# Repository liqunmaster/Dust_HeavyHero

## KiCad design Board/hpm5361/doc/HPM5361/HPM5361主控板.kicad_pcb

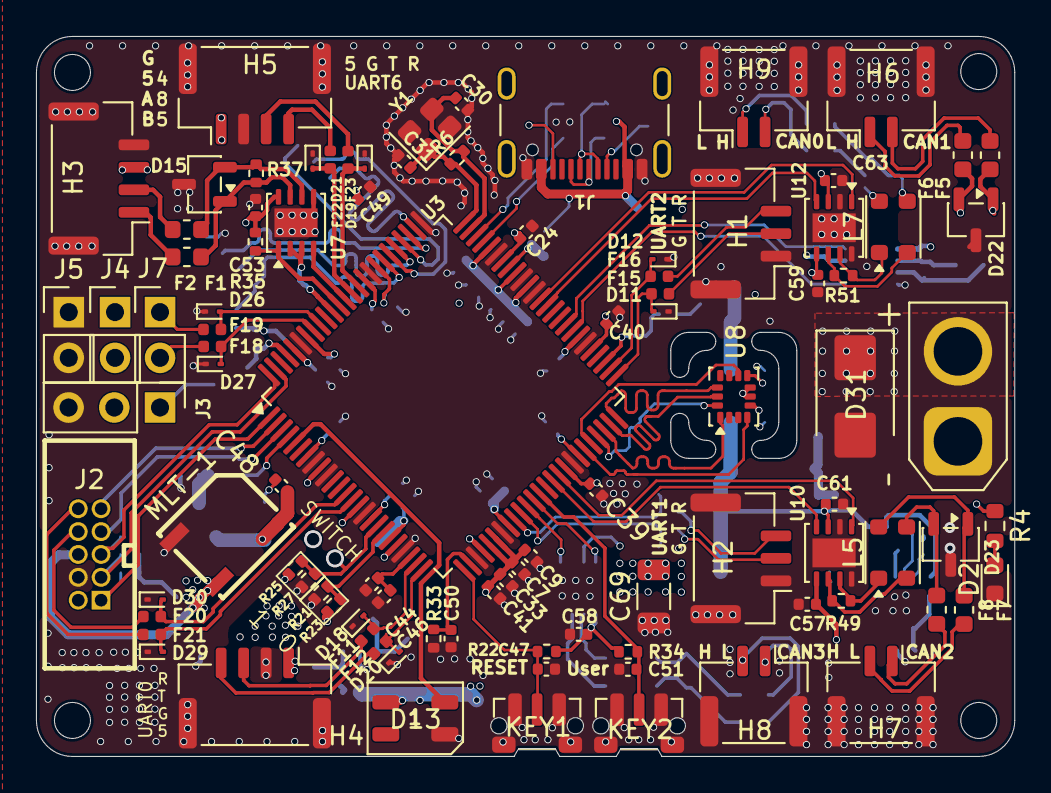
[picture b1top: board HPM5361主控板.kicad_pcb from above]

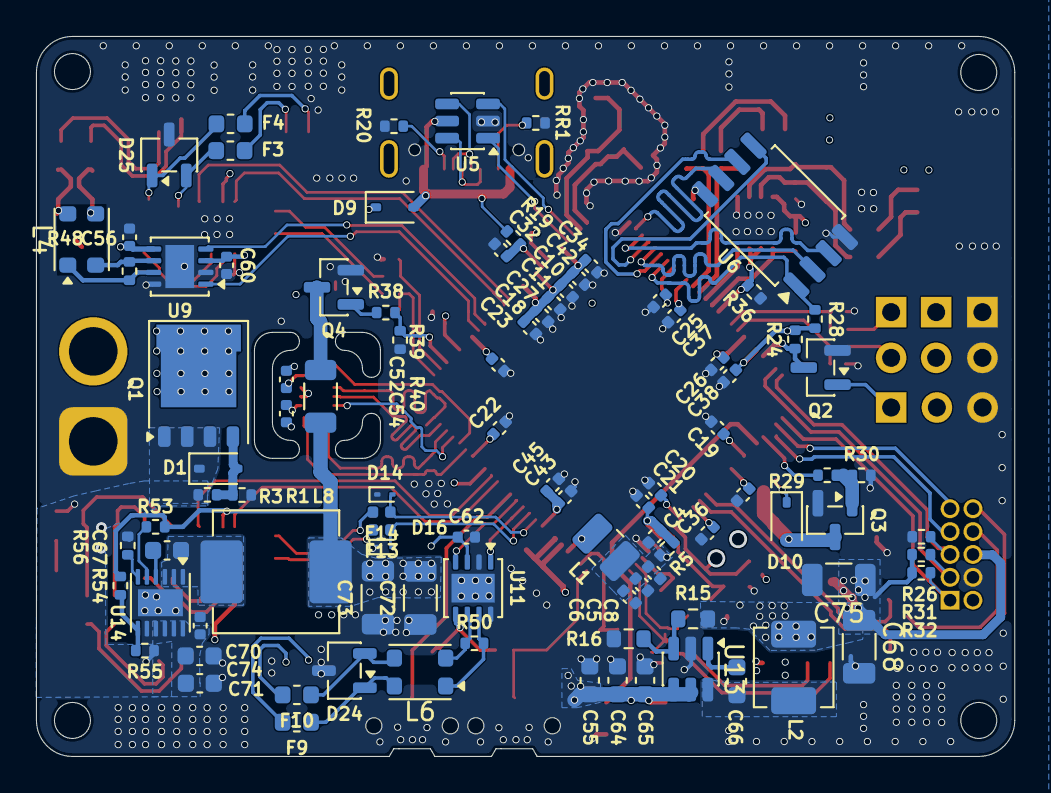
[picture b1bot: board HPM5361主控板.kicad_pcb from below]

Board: 4 copper layers, 54.3 x 40.0 mm, 189 parts (94 on the bottom side), 124 nets.

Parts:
C4, C34, C41: 10uF; C_0402_1005Metric
C5, C6, C9: 22uF; C_0402_1005Metric
C7, C8, C11, C18, C19, C20, C21, C22, C23, C24, C25, C26, C32, C33, C35, C36, C37, C38, C39, C40, C42, C43, C44, C47, C48, C49, C50, C51, C52, C53, C54, C56, C57, C58, C59, C60, C61, C62, C63, C70: 100nF; C_0402_1005Metric
C10, C27, C45, C46: 4.7uF; C_0402_1005Metric
C30, C31: 12pF; C_0402_1005Metric
C55, C64, C65: 10uF; C_0603_1608Metric
C66, C67: 100nF; C_0603_1608Metric
C68, C75: 22uF 10V; C_1206_3216Metric
C69: 47uF; C_1206_3216Metric
C71, C74: 4.7uF; C_0603_1608Metric
C72, C73: 22uF; C_1206_3216Metric
D1: BZT52C12S WH; D_SOD-323
D2: Blue; LED_0603_1608Metric
D9: SD103AWS; D_SOD-323
D10: SD103AWS S4; D_SOD-323
D11, D12, D14, D16, D18, D19, D20, D21, D26, D27, D29, D30: ESD9B5.0ST5G; D_SOD-923
D13: WS2812B; LED_WS2812B-Mini_PLCC4_3.5x3.5mm
D15: PSM712; SOT-23-3
D22, D23, D24, D25: PESD1CAN; SOT-23-3
D31: SMBJ30A; D_SMB
F1, F2, F3, F4, F5, F6, F7, F8, F9, F10: BSMD0603-005-15V; Fuse_0603_1608Metric
F11, F12, F13, F14, F15, F16, F18, F19, F20, F21, F22, F23: SMD0402; Fuse_0402_1005Metric
H1, H2: JST_GH_BM03B-GHS-TBT_1x03-1MP_P1.25mm_Vertical
H3, H4, H5: JST_GH_BM04B-GHS-TBT_1x04-1MP_P1.25mm_Vertical
H6, H7, H8, H9: JST_GH_BM02B-GHS-TBT_1x02-1MP_P1.25mm_Vertical
J1: USB_C_Receptacle_USB2.0_16P; USB_C_Receptacle_GCT_USB4105-xx-A_16P_TopMnt_Horizontal
J2: Conn_02x05_Counter_Clockwise_MountingPin; CONN-TH_10P-P1.27_HX-JN1.27-2X5P-ZZ-H4.9
J3: Conn_01x03_Pin; PinHeader_1x03_P2.54mm_Vertical
J4, J5, J7: Conn_01x02_Pin; PinHeader_1x02_P2.54mm_Vertical
KEY1, KEY2: 笑脸开关3*5; SW_Push_1P1T-MP_NO_Horizontal_Alps_SKRTLAE010
L1: NLV25T-4R7J-PF; L_1008_2520Metric
L2: 4.7uH; L_APV_APH0420
L4, L5, L6, L7: ACM2012(90欧); L_CommonModeChoke_Coilank_ACM3225
L8: 3.3UH; L_APV_APH0630
MLT-1: BUZ-SMD_L5.0-W5.5-P4.60
Q1: AGM60P100A; PQFN-8-EP_6x5mm_P1.27mm_Generic
Q2, Q3: PMBT3904; SOT-23
Q4: AO3404A; SOT-23
R1, R3, R19, R22, R26, R28, R30, R31, R32, R34, R35, R36, R39: 10K; R_0402_1005Metric
R4: 10K; R_0603_1608Metric
R5, R23, R25: 0; R_0402_1005Metric
R6: 1M; R_0402_1005Metric
R15: 62K; R_0603_1608Metric
R16: 20K; R_0603_1608Metric
R20, R24: 4.7K; R_0402_1005Metric
R21, R27, R33: 10k; R_0402_1005Metric
R29: 1K; R_0402_1005Metric
R37, R48, R49, R50, R51: 120; R_0402_1005Metric
R38: 33R; R_0402_1005Metric
R40: 36R; R_1206_3216Metric
R53, R54: 100K; R_0402_1005Metric
R55: 19.1K; R_0402_1005Metric
R56: 14.7K; R_0402_1005Metric
RR1: 4.7K; R_0402_1005Metric
U3: HPM5361ICB1; LQFP-100_14x14mm_P0.5mm
U5: USBLC6-2SC6; SOT-23-6
U6: W25Q128JVS; SOIC-8_5.3x5.3mm_P1.27mm
U7: SN65HVD75DRBR; VSON-8-1EP_3x3mm_P0.65mm_EP1.6x2.4mm
U8: ICM-42688P-HXY; LGA-14_3x2.5mm_P0.5mm_LayoutBorder3x4y
U9, U10, U11, U12: TJA1042TK-3; HVSON-8-1EP_3x3mm_P0.65mm_EP1.6x2.4mm
U13: RY8411; SOT-23-6
U14: LMR51450; WSON-12-1EP_3x3mm_P0.5mm_EP1.5x2.5mm
XT1: AMASS_XT30U-M_1x02_P5.0mm_Vertical
Y1: 24M; Crystal_SMD_2520-4Pin_2.5x2.0mm

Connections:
+3.3V: C7.2, C9.2, C10.1, C11.1, C18.2, C27.2, C33.1, C34.1, C35.2, C36.2, C37.2, C38.2, C39.2, C40.2, C41.1, C42.1, C48.1, C49.1, C52.1, C53.1, C54.1, C56.2, C57.2, C58.2, C59.2, C68.1, C75.1, D10.1 (K), J2.8, L2.2, MLT-1.1 (+), R15.2, R22.2, R23.2, R24.2, R25.2, R28.2, R31.2, R32.2, R34.2, R35.2, U3.9 (VIO_B00), U3.15 (VIO_B00), U3.30 (DCDC_IN), U3.31 (VPMC), U3.42 (VIO_B01), U3.55 (VIO_B01), U3.65 (VREFH), U3.67 (VANA), U3.71 (VPLL), U3.85 (VIO_B00), U3.96 (VIO_B00), U6.8 (VCC), U7.8 (VCC), U8.5 (VDDIO), U8.8 (VDD), U9.5 (VIO), U10.5 (VIO), U11.5 (VIO), U12.5 (VIO)
+5V: C55.1, C60.1, C61.1, C62.1, C63.1, C64.1, C65.1, C69.2, C72.2, C73.2, D9.1 (K), D13.1 (VDD), H3.3, H4.1, H5.1, J2.10, J3.2, J4.1, J4.2, L8.2, R40.1, R53.2, R54.2, U9.3 (VCC), U10.3 (VCC), U11.3 (VCC), U12.3 (VCC), U13.4 (EN), U13.5 (IN)
A: F2.2, H3.2
B: F1.2, H3.1
BOOT0: R21.1, R23.1, U3.19 (PA02/TMR1.COMP1/URT0.DE/URT0.RTS/I2C0.S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)
BOOT1: R25.1, R27.2, U3.18 (PA03/TMR1.CAPT1/URT0.CTS/I2C0.SDA/SPI3.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)
CAN0_H: F3.2, H9.2
CAN0_L: F4.2, H9.1
CAN0_RXD: U3.62 (PB01/TMR1.CAPT0/URT0.RXD/CAN0.RXD/PWM0.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), U12.4 (RXD)
CAN0_TXD: U3.63 (PB00/TMR1.COMP0/URT0.TXD/CAN0.TXD/PWM0.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), U12.1 (TXD)
CAN1_H: F5.2, H6.2
CAN1_L: F6.2, H6.1
CAN1_RXD: U3.59 (PB04/URT1.CTS/SPI3.CS0/CAN1.RXD/PWM0.P4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), U9.4 (RXD)
CAN1_TXD: U3.58 (PB05/TMR1.COMP2/URT1.DE/URT1.RTS/SPI3.S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), U9.1 (TXD)
CAN2_H: F7.2, H7.2
CAN2_L: F8.2, H7.1
CAN2_RXD: U3.40 (PY01/TMR3.CAPT0/URT0.RXD/CAN2.RXD/PWM0.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), U10.4 (RXD)
CAN2_TXD: U3.41 (PY00/TMR3.COMP0/URT0.TXD/CAN2.TXD/PWM0.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), U10.1 (TXD)
CAN3_H: F9.2, H8.2
CAN3_L: F10.2, H8.1
CAN3_RXD: U3.37 (PY04/URT1.CTS/SPI2.CS0/CAN3.RXD/PWM0.P4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), U11.4 (RXD)
CAN3_TXD: U3.36 (PY05/TMR3.COMP2/URT1.DE/URT1.RTS/SPI2.S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), U11.1 (TXD)
DBUS: J3.1, Q2.1 (B)
DCDC_LP: L1.2, U3.29 (DCDC_LP)
GND: C4.1, C5.1, C6.1, C7.1, C8.1, C9.1, C10.2, C11.2, C18.1, C19.2, C20.2, C21.2, C22.2, C23.2, C24.2, C25.2, C26.2, C27.1, C30.2, C31.1, C32.1, C33.2, C34.2, C35.1, C36.1, C37.1, C38.1, C39.1, C40.1, C41.2, C42.2, C43.1, C44.1, C45.1, C46.1, C47.2, C49.2, C50.1, C51.2, C52.2, C53.2, C54.2, C55.2, C56.1, C57.1, C58.1, C59.1, C60.2, C61.2, C62.2, C63.2, C64.2, C65.2, C68.2, C69.1, C70.1, C71.1, C72.1, C73.1, C74.1, C75.2, D2.1 (K), D11.1 (A1), D12.1 (A1), D13.3 (VSS), D14.1 (A1), D15.3 (A), D16.1 (A1), D18.1 (A1), D19.1 (A1), D20.1 (A1), D21.1 (A1), D22.3 (A), D23.3 (A), D24.3 (A), D25.3 (A), D26.1 (A1), D27.1 (A1), D29.1 (A1), D30.1 (A1), D31.2 (A2), H1.1, H1.MP, H2.1, H2.MP, H3.4, H3.MP, H4.2, H4.MP, H5.2, H5.MP, H6.MP, H7.MP, H8.MP, H9.MP, J1.A1 (GND), J1.A12 (GND), J1.B1 (GND), J1.B12 (GND), J2.9, J3.3, J5.1, J5.2, KEY1.1, KEY1.MP, KEY2.1, KEY2.MP, MLT-1.3 (NC), Q2.2 (E), Q3.2 (E), Q4.2 (S), R1.2, R16.1, R20.2, R21.2, R26.2, R27.1, R30.2, R33.1, R36.1, R39.1, R55.1, R56.1, RR1.2, U3.8 (VSS), U3.10 (VSS), U3.16 (VSS), U3.22 (VSS), U3.28 (DCDC_GND), U3.32 (VSS), U3.43 (VSS), U3.56 (VSS), U3.64 (VREFL), U3.66 (VSS), U3.70 (VSS), U3.76 (VSS), U3.84 (VSS), U3.95 (VSS), U5.2 (GND), U6.4 (GND), U7.5 (GND), U7.9 (PAD), U8.6 (GNDIO), U8.7 (GND), U9.2 (GND), U9.8 (STB), U9.9 (GND), U10.2 (GND), U10.8 (STB), U10.9 (GND), U11.2 (GND), U11.8 (STB), U11.9 (GND), U12.2 (GND), U12.8 (STB), U12.9 (GND), U13.2 (GND), U14.8 (GND), U14.13 (PAD), XT1.1 (-), Y1.2, Y1.4
INT1: U3.45 (PB15/TMR0.COMP3/URT3.TXD/SPI2.DAT3/CAN3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), U8.4 (INT1)
INT2: U3.46 (PB14/URT3.RXD/SPI2.DAT2/CAN3.RXD/PWM0.F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), U8.9 (INT2)
JTAG_TCK: J2.3, R26.1, U3.100 (PA06/TMR0.CAPT0/URT1.RXD/I2C1.SDA/SPI0.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)
JTAG_TDI: J2.1, R32.1, U3.1 (PA05/TMR1.COMP2/URT1.DE/URT1.RTS/SPI0.S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)
JTAG_TDO: J2.5, U3.2 (PA04/URT1.CTS/SPI0.CS0/CAN1.RXD/PWM0.P0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)
JTAG_TMS: J2.2, R31.1, U3.99 (PA07/TMR0.COMP0/URT1.TXD/I2C1.SCL/SPI0.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)
JTAG_TRST: J2.4, U3.3 (PA08/TMR0.COMP1/URT2.TXD/I2C2.SCL/SPI3.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)
unnamed: C67.2, L8.1, U14.1 (SW), U14.2 (SW), U14.3 (SW)
unnamed: D1.2 (A), Q1.G, R1.1, R3.2
unnamed: D2.2 (A), R4.2
unnamed: C48.2, D10.2 (A), MLT-1.2 (-), Q3.3 (C)
unnamed: D22.1 (K), F5.1, L4.4
unnamed: D22.2 (K), F6.1, L4.3
unnamed: D23.1 (K), F7.1, L5.4
unnamed: D23.2 (K), F8.1, L5.3
unnamed: D24.1 (K), F9.1, L6.4
unnamed: D24.2 (K), F10.1, L6.3
unnamed: D25.1 (K), F4.1, L7.3
unnamed: D25.2 (K), F3.1, L7.4
unnamed: F11.2, H4.3
unnamed: F12.2, H4.4
unnamed: F13.2, H2.2
unnamed: F14.2, H2.3
unnamed: F15.2, H1.2
unnamed: F16.2, H1.3
unnamed: F22.2, H5.3
unnamed: F23.2, H5.4
unnamed: J1.A5 (CC1), R20.1
unnamed: J1.B5 (CC2), RR1.1
unnamed: J1.A6 (D+), J1.B6 (D+), U5.6 (I/O1)
unnamed: J1.A7 (D-), J1.B7 (D-), U5.4 (I/O2)
unnamed: F21.1, J2.6
unnamed: F20.1, J2.7
unnamed: F19.2, J7.1
unnamed: F18.2, J7.2
unnamed: Q3.1 (B), R29.1, R30.1
unnamed: Q4.3 (D), R40.2
unnamed: Q4.1 (G), R38.1
unnamed: C5.2, C6.2, C8.2, L1.1, R5.2, U3.21 (DCDC_SNS)
unnamed: C32.2, R19.2, U3.68 (USBVBUS)
unnamed: C30.1, R6.2, U3.74 (XTALI), Y1.3
unnamed: C31.2, R6.1, U3.75 (XTALO), Y1.1
unnamed: C44.2, C46.2, U3.23 (VDD_OTPCAP)
unnamed: C43.2, C45.2, U3.33 (VDD_PMCCAP)
unnamed: D15.2 (K), F2.1, R37.1, U7.6 (A)
unnamed: D15.1 (K), F1.1, R37.2, U7.7 (B)
unnamed: L4.1, R48.2, U9.7 (CANH)
unnamed: L4.2, R48.1, U9.6 (CANL)
unnamed: L5.1, R49.2, U10.7 (CANH)
unnamed: L5.2, R49.1, U10.6 (CANL)
unnamed: L6.1, R50.2, U11.7 (CANH)
unnamed: L6.2, R50.1, U11.6 (CANL)
unnamed: L7.1, R51.2, U12.7 (CANH)
unnamed: L7.2, R51.1, U12.6 (CANL)
unnamed: C66.2, U13.1 (BS)
unnamed: R15.1, R16.2, U13.3 (FB)
unnamed: C66.1, L2.1, U13.6 (LX)
unnamed: C67.1, U14.4 (BOOT)
unnamed: R54.1, R55.2, U14.7 (FB)
unnamed: R53.1, U14.5 (PG)
unnamed: R56.2, U14.6 (RT)
PWM0_P5: R29.2, U3.4 (PA09/TMR0.CAPT1/URT2.RXD/I2C2.SDA/SPI3.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)
PWM0_P6: D13.4 (DIN), U3.5 (PA10/TMR0.COMP2/URT2.DE/URT2.RTS/SPI3.C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)
PWM0_P7: R38.2, R39.2, U3.53 (PB07/TMR0.COMP0/URT1.TXD/I2C1.SCL/SPI3.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)
PWM1_P2: D27.2 (A2), F18.1, U3.93 (PA18/TMR3.COMP1/URT4.DE/URT4.RTS/I2C0.S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)
PWM1_P3: D26.2 (A2), F19.1, U3.92 (PA19/TMR3.CAPT1/URT4.CTS/I2C0.SDA/SPI1.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)
RESET: C47.1, KEY1.2, R22.1, U3.26 (RESETN)
SPI1_CS: R28.1, U3.82 (PA26/TMR2.COMP2/URT6.DE/URT6.RTS/SPI1.C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), U6.1 (~CS)
SPI1_D2: U3.78 (PA30/URT7.RXD/SPI1.DAT2/CAN3.RXD/XPI0.C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), U6.3 (~WP/IO_{2})
SPI1_D3: U3.77 (PA31/TMR2.COMP3/URT7.TXD/SPI1.DAT3/CAN3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), U6.7 (~HOLD/~RESET/IO_{3})
SPI1_MISO: U3.80 (PA28/URT7.CTS/I2C3.SDA/SPI1.MISO/XPI0.C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), U6.2 (DO/IO_{1})
SPI1_MOSI: U3.79 (PA29/TMR3.COMP3/URT7.DE/URT7.RTS/I2C3.S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), U6.5 (DI/IO_{0})
SPI1_SCLK: U3.81 (PA27/URT6.CTS/SPI1.SCLK/XPI0.CA_SCLK/PW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), U6.6 (CLK)
SPI2_CS: U3.50 (PB10/TMR0.COMP2/URT2.DE/URT2.RTS/SPI2.C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), U8.12 (CSB)
SPI2_MISO: U3.48 (PB12/URT3.CTS/I2C3.SDA/SPI2.MISO/PWM1.F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), U8.1 (SDO/SA0)
SPI2_MOSI: U3.47 (PB13/TMR1.COMP3/URT3.DE/URT3.RTS/I2C3.S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), U8.14 (SDX)
SPI2_SCLK: U3.49 (PB11/URT2.CTS/SPI2.SCLK/ACMP.COMP1/PWM1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), U8.13 (SCX)
UART0_RXD: D18.2 (A2), F11.1, U3.24 (PA01/TMR1.CAPT0/URT0.RXD/CAN0.RXD/PWM0.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)
UART0_TXD: D20.2 (A2), F12.1, U3.25 (PA00/TMR1.COMP0/URT0.TXD/CAN0.TXD/PWM0.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)
UART1_RXD: D16.2 (A2), F13.1, U3.35 (PY06/TMR2.CAPT0/URT1.RXD/I2C3.SDA/SPI2.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)
UART1_TXD: D14.2 (A2), F14.1, U3.34 (PY07/TMR2.COMP0/URT1.TXD/I2C3.SCL/SPI2.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)
UART2_RXD: D11.2 (A2), F15.1, U3.51 (PB09/TMR0.CAPT1/URT2.RXD/I2C2.SDA/SPI2.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)
UART2_TXD: D12.2 (A2), F16.1, U3.52 (PB08/TMR0.COMP1/URT2.TXD/I2C2.SCL/SPI2.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)
UART3_RXD: D30.2 (A2), F20.2, U3.13 (PA14/URT3.RXD/SPI3.DAT2/CAN3.RXD/PWM0.P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)
UART3_TXD: D29.2 (A2), F21.2, U3.14 (PA15/TMR0.COMP3/URT3.TXD/SPI3.DAT3/CAN3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)
UART4_RXD: Q2.3 (C), R24.1, U3.97 (PA17/TMR3.CAPT0/URT4.RXD/CAN0.RXD/PWM0.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)
UART5_DE: R36.2, U3.90 (PA21/TMR3.COMP2/URT5.DE/URT5.RTS/SPI2.S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), U7.2 (#RE), U7.3 (DE)
UART5_RXD: R35.1, U3.89 (PA22/TMR2.CAPT0/URT5.RXD/I2C1.SDA/SPI2.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), U7.1 (R_OUT)
UART5_TXD: U3.88 (PA23/TMR2.COMP0/URT5.TXD/I2C1.SCL/SPI2.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), U7.4 (D_IN)
UART6_RXD: D19.2 (A2), F22.1, U3.86 (PA25/TMR2.CAPT1/URT6.RXD/I2C2.SDA/SPI1.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)
UART6_TXD: D21.2 (A2), F23.1, U3.87 (PA24/TMR2.COMP1/URT6.TXD/I2C2.SCL/SPI1.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)
USB_DM: U3.73 (USB_DM), U5.3 (I/O2)
USB_DP: U3.72 (USB_DP), U5.1 (I/O1)
User_Key: C51.1, KEY2.2, R34.1, U3.38 (PY03/TMR3.CAPT1/URT0.CTS/I2C2.SDA/CAN3.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)
VBUS: D9.2 (A), J1.A4 (VBUS), J1.A9 (VBUS), J1.B4 (VBUS), J1.B9 (VBUS), R19.1, U5.5 (VBUS)
VDD_SOC: C4.2, C19.1, C20.1, C21.1, C22.1, C23.1, C24.1, C25.1, C26.1, R5.1, U3.7 (VDD_SOC), U3.17 (VDD_SOC), U3.20 (VDD_SOC), U3.44 (VDD_SOC), U3.57 (VDD_SOC), U3.69 (VDD_SOC), U3.83 (VDD_SOC), U3.94 (VDD_SOC)
VIN: C70.2, C71.2, C74.2, D1.1 (K), Q1.S, R3.1, R4.1, U14.9 (EN), U14.10 (VIN), U14.11 (VIN), U14.12 (VIN)
VIN1: D31.1 (A1), Q1.D, XT1.2 (+)
WAKEUP: C50.2, R33.2, U3.27 (WAKEUP)

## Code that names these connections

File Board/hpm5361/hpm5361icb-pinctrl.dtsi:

/*
 * Copyright 2026 Dust Robotics
 * SPDX-License-Identifier: Apache-2.0
 *
 * Dust HeavyHero HPM5361ICB pinmux definitions.
 * Default wiring from the board schematic. Application overlays may replace
 * a peripheral state when a different operating mode is required.
 */

#include "dt-bindings/pinctrl/hpmicro-pinctrl-common.h"

&pinctrl {
	/* UART0 ISP header: PA00 TX, PA01 RX. */
	pinmux_uart0: pinmux_uart0 {
		group0 {
			pinmux = <HPMICRO_PINMUX(HPMICRO_PIN(HPMICRO_PORTA, 0), IOC_TYPE_IOC, 0, 2)>,
				 <HPMICRO_PINMUX(HPMICRO_PIN(HPMICRO_PORTA, 1), IOC_TYPE_IOC, 0, 2)>;
		};
	};

	/* UART1 external header: PY07 TX, PY06 RX. */
	pinmux_uart1: pinmux_uart1 {
		group0 {
			pinmux = <HPMICRO_PINMUX(HPMICRO_PIN(HPMICRO_PORTY, 7), IOC_TYPE_IOC, 0, 2)>,
				 <HPMICRO_PINMUX(HPMICRO_PIN(HPMICRO_PORTY, 6), IOC_TYPE_IOC, 0, 2)>;
		};
	};

	/* UART2: VT02/VT03 shared figure-transmission interface (PB08/PB09 ALT2) */
	pinmux_uart2: pinmux_uart2 {
		group0 {
			pinmux = <HPMICRO_PINMUX(HPMICRO_PIN(HPMICRO_PORTB, 8), IOC_TYPE_IOC, 0, 2)>,
				 <HPMICRO_PINMUX(HPMICRO_PIN(HPMICRO_PORTB, 9), IOC_TYPE_IOC, 0, 2)>;
		};
	};

	/* UART3: debug console / redefined printf (PA14/PA15 ALT2) */
	pinmux_uart3: pinmux_uart3 {
		group0 {
			pinmux = <HPMICRO_PINMUX(HPMICRO_PIN(HPMICRO_PORTA, 14), IOC_TYPE_IOC, 0, 2)>,
				 <HPMICRO_PINMUX(HPMICRO_PIN(HPMICRO_PORTA, 15), IOC_TYPE_IOC, 0, 2)>;
		};
	};

	/* UART4: DT7 remote receiver (PA16/PA17 ALT2) */
	pinmux_uart4: pinmux_uart4 {
		group0 {
			pinmux = <HPMICRO_PINMUX(HPMICRO_PIN(HPMICRO_PORTA, 16), IOC_TYPE_IOC, 0, 2)>,
				 <HPMICRO_PINMUX(HPMICRO_PIN(HPMICRO_PORTA, 17), IOC_TYPE_IOC, 0, 2)>;
		};
	};

	/* UART5: PA23 TX, PA22 RX, PA21 DE. */
	pinmux_uart5: pinmux_uart5 {
		group0 {
			pinmux = <HPMICRO_PINMUX(HPMICRO_PIN(HPMICRO_PORTA, 23), IOC_TYPE_IOC, 0, 2)>,
				 <HPMICRO_PINMUX(HPMICRO_PIN(HPMICRO_PORTA, 22), IOC_TYPE_IOC, 0, 2)>,
				 <HPMICRO_PINMUX(HPMICRO_PIN(HPMICRO_PORTA, 21), IOC_TYPE_IOC, 0, 2)>;
		};
	};

	/* UART6: PA24 TX, PA25 RX. */
	pinmux_uart6: pinmux_uart6 {
		group0 {
			pinmux = <HPMICRO_PINMUX(HPMICRO_PIN(HPMICRO_PORTA, 24), IOC_TYPE_IOC, 0, 2)>,
				 <HPMICRO_PINMUX(HPMICRO_PIN(HPMICRO_PORTA, 25), IOC_TYPE_IOC, 0, 2)>;
		};
	};

	/* SPI1: W25Q128 log flash, including the quad data pins. */
	pinmux_spi1: pinmux_spi1 {
		group0 {
			pinmux = <HPMICRO_PINMUX(HPMICRO_PIN(HPMICRO_PORTA, 26), IOC_TYPE_IOC, 0, 5)>,
				 <HPMICRO_PINMUX(HPMICRO_PIN(HPMICRO_PORTA, 27), IOC_TYPE_IOC, 0, 5)>,
				 <HPMICRO_PINMUX(HPMICRO_PIN(HPMICRO_PORTA, 28), IOC_TYPE_IOC, 0, 5)>,
				 <HPMICRO_PINMUX(HPMICRO_PIN(HPMICRO_PORTA, 29), IOC_TYPE_IOC, 0, 5)>,
				 <HPMICRO_PINMUX(HPMICRO_PIN(HPMICRO_PORTA, 30), IOC_TYPE_IOC, 0, 5)>,
				 <HPMICRO_PINMUX(HPMICRO_PIN(HPMICRO_PORTA, 31), IOC_TYPE_IOC, 0, 5)>;
		};
	};

	/* SPI2: ICM-42688P-HXY IMU (PB13/12/11/10 = MOSI/MISO/SCLK/CS_0 ALT5) */
	pinmux_spi2: pinmux_spi2 {
		group0 {
			pinmux = <HPMICRO_PINMUX(HPMICRO_PIN(HPMICRO_PORTB, 13), IOC_TYPE_IOC, 0, 5)>,
				 <HPMICRO_PINMUX(HPMICRO_PIN(HPMICRO_PORTB, 12), IOC_TYPE_IOC, 0, 5)>,
				 <HPMICRO_PINMUX(HPMICRO_PIN(HPMICRO_PORTB, 11), IOC_TYPE_IOC, 0, 5)>,
				 <HPMICRO_PINMUX(HPMICRO_PIN(HPMICRO_PORTB, 10), IOC_TYPE_IOC, 0, 5)>;
		};
	};

	pinmux_board_can0: pinmux_board_can0 {
		group0 {
			pinmux = <HPMICRO_PINMUX(HPMICRO_PIN(HPMICRO_PORTB, 0), IOC_TYPE_IOC, 0, 7)>,
				 <HPMICRO_PINMUX(HPMICRO_PIN(HPMICRO_PORTB, 1), IOC_TYPE_IOC, 0, 7)>;
		};
	};

	pinmux_board_can1: pinmux_board_can1 {
		group0 {
			pinmux = <HPMICRO_PINMUX(HPMICRO_PIN(HPMICRO_PORTB, 5), IOC_TYPE_IOC, 0, 7)>,
				 <HPMICRO_PINMUX(HPMICRO_PIN(HPMICRO_PORTB, 4), IOC_TYPE_IOC, 0, 7)>;
		};
	};

	pinmux_board_can2: pinmux_board_can2 {
		tx {
			pinmux = <HPMICRO_PINMUX(HPMICRO_PIN(HPMICRO_PORTY, 0), IOC_TYPE_IOC, 0, 7)>;
		};
		rx {
			pinmux = <HPMICRO_PINMUX(HPMICRO_PIN(HPMICRO_PORTY, 1), IOC_TYPE_IOC, 0, 7)>;
			input-enable;
		};
		pioc {
			pinmux = <HPMICRO_PINMUX(HPMICRO_PIN(HPMICRO_PORTY, 0), IOC_TYPE_PIOC, 0, 3)>,
				 <HPMICRO_PINMUX(HPMICRO_PIN(HPMICRO_PORTY, 1), IOC_TYPE_PIOC, 0, 3)>;
		};
	};

	pinmux_board_can3: pinmux_board_can3 {
		tx {
			pinmux = <HPMICRO_PINMUX(HPMICRO_PIN(HPMICRO_PORTY, 5), IOC_TYPE_IOC, 0, 7)>;
		};
		rx {
			pinmux = <HPMICRO_PINMUX(HPMICRO_PIN(HPMICRO_PORTY, 4), IOC_TYPE_IOC, 0, 7)>;
			input-enable;
		};
		pioc {
			pinmux = <HPMICRO_PINMUX(HPMICRO_PIN(HPMICRO_PORTY, 5), IOC_TYPE_PIOC, 0, 3)>,
				 <HPMICRO_PINMUX(HPMICRO_PIN(HPMICRO_PORTY, 4), IOC_TYPE_PIOC, 0, 3)>;
		};
	};

	/* PWM0: PA09 P5, PA10 P6, PB07 P7. */
	pinmux_pwm0: pinmux_pwm0 {
		group0 {
			pinmux = <HPMICRO_PINMUX(HPMICRO_PIN(HPMICRO_PORTA, 9), IOC_TYPE_IOC, 0, 16)>,
				 <HPMICRO_PINMUX(HPMICRO_PIN(HPMICRO_PORTA, 10), IOC_TYPE_IOC, 0, 16)>,
				 <HPMICRO_PINMUX(HPMICRO_PIN(HPMICRO_PORTB, 7), IOC_TYPE_IOC, 0, 16)>;
		};
	};

	/* PWM1: PA19 P3, PA20 P4. */
	pinmux_pwm1: pinmux_pwm1 {
		group0 {
			pinmux = <HPMICRO_PINMUX(HPMICRO_PIN(HPMICRO_PORTA, 19), IOC_TYPE_IOC, 0, 17)>,
				 <HPMICRO_PINMUX(HPMICRO_PIN(HPMICRO_PORTA, 20), IOC_TYPE_IOC, 0, 17)>;
		};
	};

	/* GPIOB: PB15/PB14 = ICM-42688P-HXY INT1/INT2 (EXTI input) */
	pinmux_gpiob: pinmux_gpiob {
		group0 {
			pinmux = <HPMICRO_PINMUX(HPMICRO_PIN(HPMICRO_PORTB, 15), IOC_TYPE_IOC, 0, 0)>,
				 <HPMICRO_PINMUX(HPMICRO_PIN(HPMICRO_PORTB, 14), IOC_TYPE_IOC, 0, 0)>;
			input-enable;
			input-schmitt-enable;
		};
	};

	/* GPIOY: PY03 = User_Key (SW2, GPIO input with pull-up) */
	pinmux_gpioy: pinmux_gpioy {
		group0 {
			pinmux = <HPMICRO_PINMUX(HPMICRO_PIN(HPMICRO_PORTY, 3), IOC_TYPE_IOC, 0, 0)>;
			bias-pull-up;
			input-enable;
			input-schmitt-enable;
		};
	};
};
